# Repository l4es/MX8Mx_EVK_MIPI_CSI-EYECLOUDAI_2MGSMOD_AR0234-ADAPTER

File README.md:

# MX8Mx_EVK_MIPI_CSI-EYECLOUDAI_2MGSMOD_AR0234-ADAPTER
Adapter board for [EyecloudAI 2MP Gobal Shutter Camera Module (AR0234CS)](https://www.crowdsupply.com/eyecloud/eyecloudai-cdk) to MiniSAS on NXP EVK

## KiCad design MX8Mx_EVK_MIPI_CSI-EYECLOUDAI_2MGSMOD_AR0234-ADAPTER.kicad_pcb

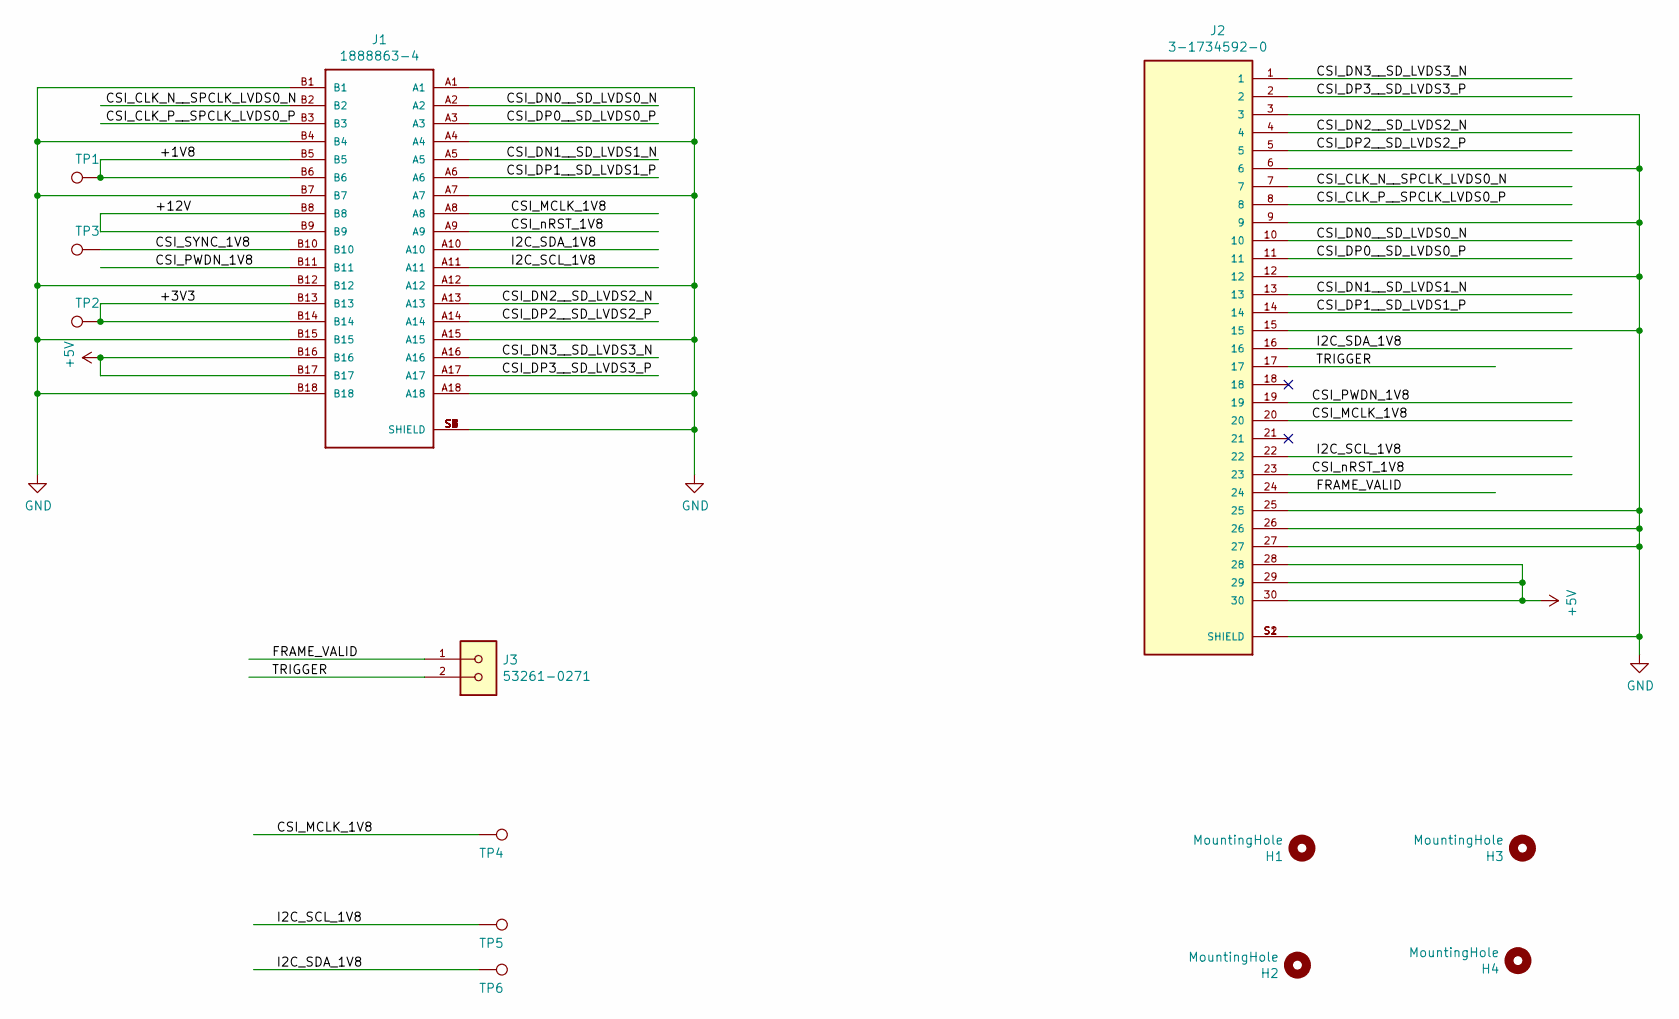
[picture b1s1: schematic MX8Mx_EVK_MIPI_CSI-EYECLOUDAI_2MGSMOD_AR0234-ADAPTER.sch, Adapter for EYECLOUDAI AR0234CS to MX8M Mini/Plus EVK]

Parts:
H1, H2, H3, H4: MountingHole; MountingHole_2.2mm_M2_Pad
J1: 1888863-4; TE_1888863-4
J2: 3-1734592-0; TE_3-1734592-0; PARTREV C
J3: 53261-0271; MOLEX_53261-0271
TP1, TP2, TP3, TP4, TP5, TP6: TestPoint; TestPoint_Pad_D1.0mm

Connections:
+5V: J1.B16, J1.B17, J2.28, J2.29, J2.30
/+1V8: J1.B5, J1.B6, TP1.1
/+3V3: J1.B13, J1.B14, TP2.1
/+12V: J1.B8, J1.B9
/CSI_CLK_N__SPCLK_LVDS0_N: J1.B2, J2.7
/CSI_CLK_P__SPCLK_LVDS0_P: J1.B3, J2.8
/CSI_DN0__SD_LVDS0_N: J1.A2, J2.10
/CSI_DN1__SD_LVDS1_N: J1.A5, J2.13
/CSI_DN2__SD_LVDS2_N: J1.A13, J2.4
/CSI_DN3__SD_LVDS3_N: J1.A16, J2.1
/CSI_DP0__SD_LVDS0_P: J1.A3, J2.11
/CSI_DP1__SD_LVDS1_P: J1.A6, J2.14
/CSI_DP2__SD_LVDS2_P: J1.A14, J2.5
/CSI_DP3__SD_LVDS3_P: J1.A17, J2.2
/CSI_MCLK_1V8: J1.A8, J2.20, TP4.1
/CSI_PWDN_1V8: J1.B11, J2.19
/CSI_SYNC_1V8: J1.B10, TP3.1
/CSI_nRST_1V8: J1.A9, J2.23
/FRAME_VALID: J2.24, J3.1
/I2C_SCL_1V8: J1.A11, J2.22, TP5.1
/I2C_SDA_1V8: J1.A10, J2.16, TP6.1
/TRIGGER: J2.17, J3.2
GND: J1.A1, J1.A4, J1.A7, J1.A12, J1.A15, J1.A18, J1.B1, J1.B4, J1.B7, J1.B12, J1.B15, J1.B18, J1.S1 (SHIELD), J1.S2 (SHIELD), J1.S3 (SHIELD), J1.S4 (SHIELD), J1.S5 (SHIELD), J1.S6 (SHIELD), J1.S7 (SHIELD), J1.S8 (SHIELD), J2.3, J2.6, J2.9, J2.12, J2.15, J2.25, J2.26, J2.27, J2.S1 (SHIELD), J2.S2 (SHIELD)

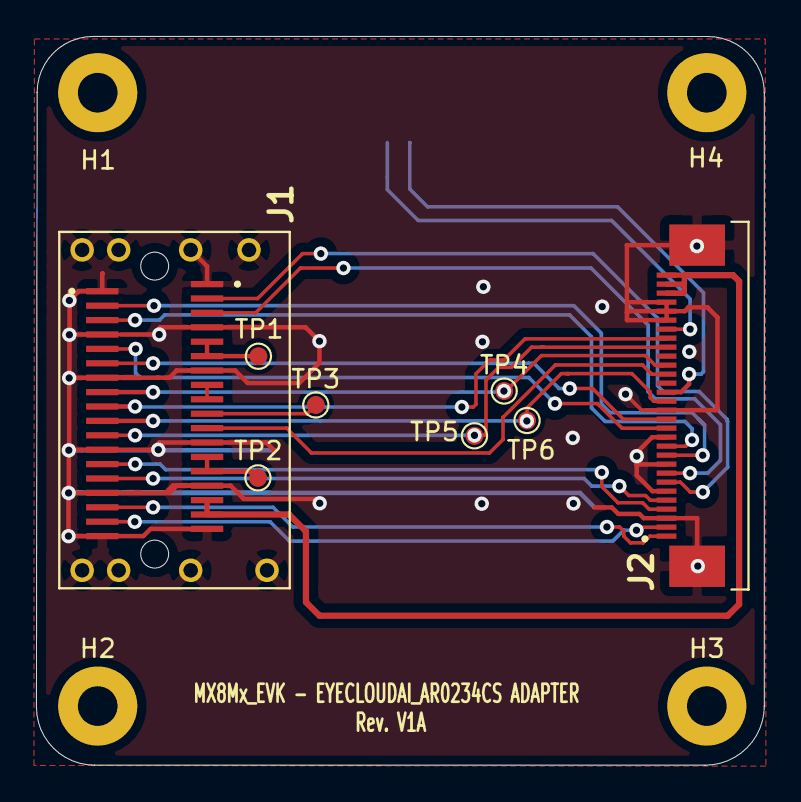
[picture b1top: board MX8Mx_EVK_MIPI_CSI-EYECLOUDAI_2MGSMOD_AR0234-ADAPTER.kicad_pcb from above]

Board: 2 copper layers, 40.4 x 40.5 mm, 13 parts (1 on the bottom side), 23 nets.

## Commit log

2021-11-12 Add more testpoints
2021-12-12 Add release V1A
2021-12-12 Add documentation
2021-12-12 Add README with illustration
